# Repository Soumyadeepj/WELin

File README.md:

# WELin

WELin is a RFID based wireless inventory mangement system designed for , developed as a course project (EE344).<br>
It consists of 

> A light-weight wireless tag scanner with a custom PN532 reader module

> A userfriendly website and android application for tracking inventory

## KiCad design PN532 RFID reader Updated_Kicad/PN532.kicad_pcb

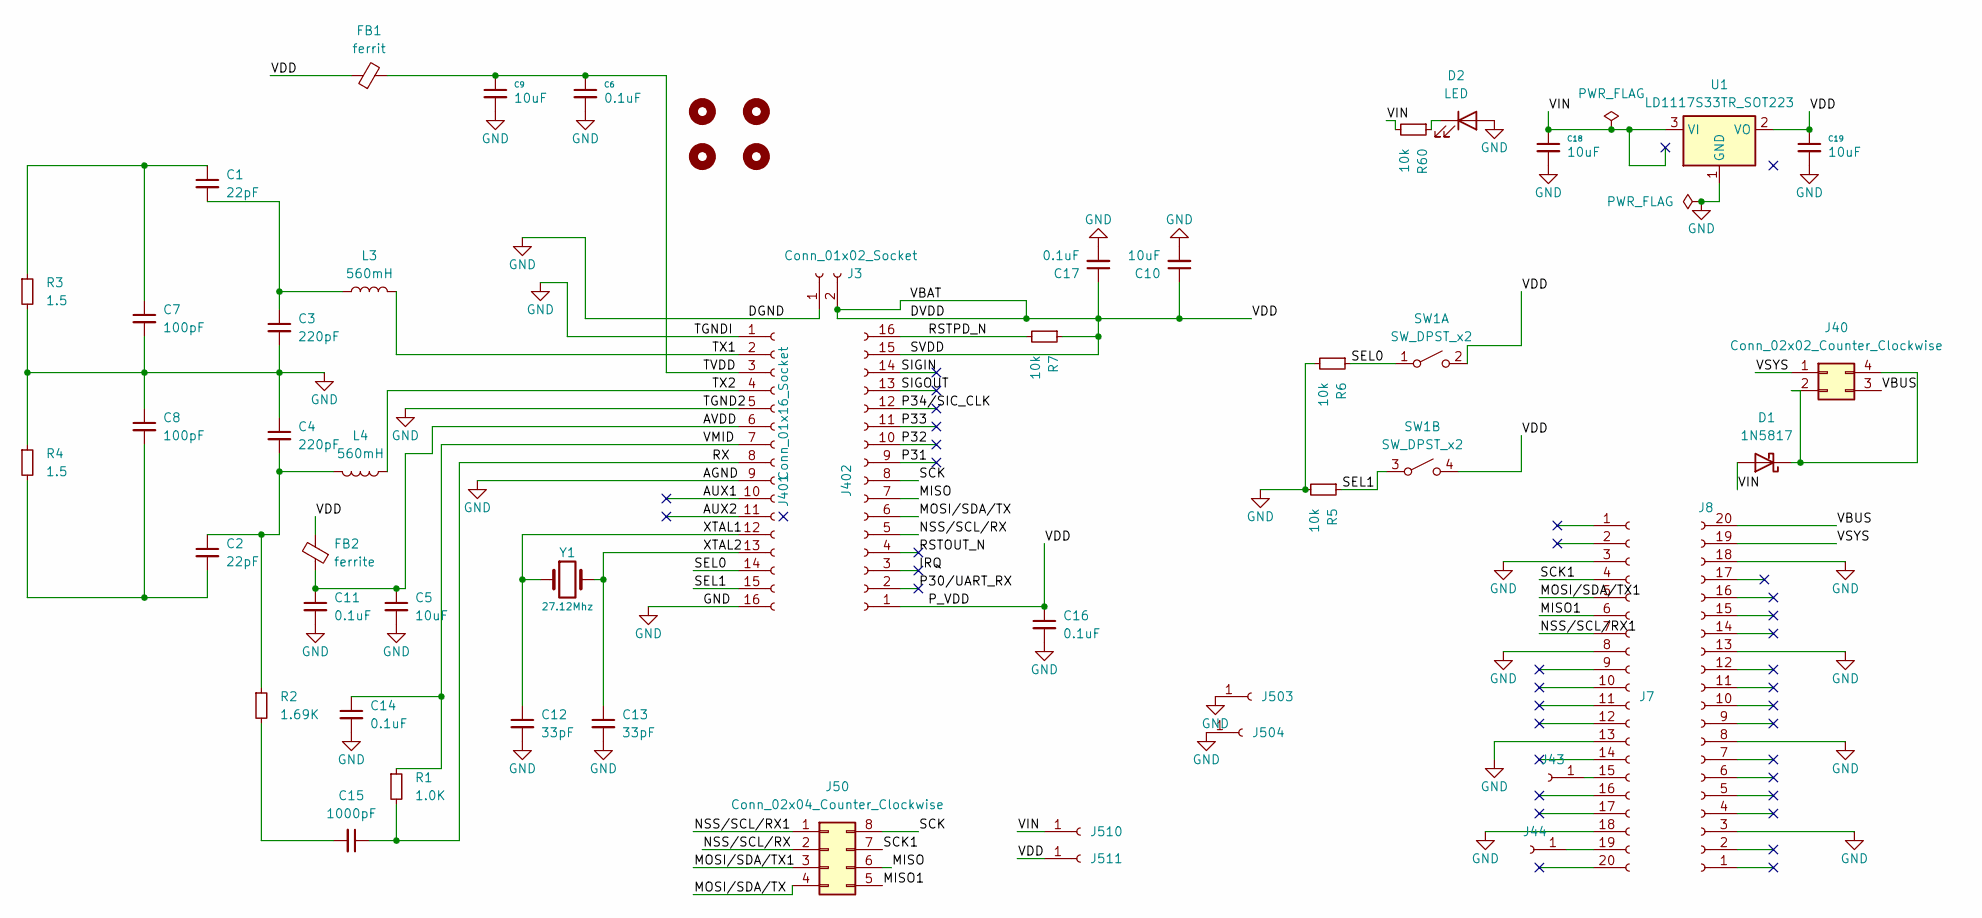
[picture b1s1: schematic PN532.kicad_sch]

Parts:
C1, C2: 22pF; C_1206_3216Metric_Pad1.33x1.80mm_HandSolder
C3, C4: 220pF; C_1206_3216Metric_Pad1.33x1.80mm_HandSolder
C5, C9, C10, C18, C19: 10uF; C_1206_3216Metric_Pad1.33x1.80mm_HandSolder
C6, C11, C14, C16, C17: 0.1uF; C_1206_3216Metric_Pad1.33x1.80mm_HandSolder
C7, C8: 100pF; C_1206_3216Metric_Pad1.33x1.80mm_HandSolder
C12, C13: 33pF; C_1206_3216Metric_Pad1.33x1.80mm_HandSolder
C15: 1000pF; C_1206_3216Metric_Pad1.33x1.80mm_HandSolder
D1: 1N5817; D_DO-41_SOD81_P10.16mm_Horizontal
D2: LED; C_0805_2012Metric_Pad1.18x1.45mm_HandSolder
FB1: ferrit; L_0805_2012Metric_Pad1.05x1.20mm_HandSolder
FB2: ferrite; L_0805_2012Metric_Pad1.05x1.20mm_HandSolder
H1, H2, H3, H4: MountingHole; MountingHole_2.5mm
J3: Conn_01x02_Socket; PinSocket_1x02_P2.54mm_Vertical
J7, J8: Conn_01x20_Socket; PinSocket_1x20_P2.54mm_Vertical
J40: Conn_02x02_Counter_Clockwise; PinSocket_2x02_P2.54mm_Vertical
J43, J44, J503, J504, J510, J511: Conn_01x01_Socket; PinSocket_1x01_P2.54mm_Vertical
J50: Conn_02x04_Counter_Clockwise; PinHeader_2x04_P2.54mm_Vertical
J401, J402: Conn_01x16_Socket; PinSocket_1x16_P2.54mm_Vertical
L3, L4: 560mH; L_0603_1608Metric_Pad1.05x0.95mm_HandSolder
R1: 1.0K; R_1206_3216Metric_Pad1.30x1.75mm_HandSolder
R2: 1.69K; R_1206_3216Metric_Pad1.30x1.75mm_HandSolder
R3, R4: 1.5; R_1206_3216Metric_Pad1.30x1.75mm_HandSolder
R5, R6, R7, R60: 10k; R_0805_2012Metric_Pad1.20x1.40mm_HandSolder
SW1: SW_DPST_x2; SW_DIP_SPSTx02_Slide_6.7x6.64mm_W7.62mm_P2.54mm_LowProfile
U1: LD1117S33TR_SOT223; SOT-223-3_TabPin2
Y1: 27.12Mhz; Crystal_HC49-U_Vertical

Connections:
/AUX1: J401.10
/AUX2: J401.11
/AVDD: C5.1, C11.1, FB2.1, J401.6
/DVDD: C10.1, C16.1, C17.1, C19.1, FB1.1, FB2.2, J3.2, J402.1, J402.15, J511.1, R7.1, SW1.2 (B), SW1.4 (B), U1.2 (VO)
/IRQ: J402.3
/MISO: J50.6, J402.7
/MISO1: J7.6, J50.5
/MOSI/SDA/TX: J50.4, J402.6
/MOSI/SDA/TX1: J7.5, J50.3
/NSS/SCL/RX: J50.2, J402.5
/NSS/SCL/RX1: J7.7, J50.1
/P30/UART_RX: J402.2
/P31: J402.9
/P32: J402.10
/P33: J402.11
/P34/SIC_CLK: J402.12
/RSTOUT_N: J402.4
/RSTPD_N: J402.16, R7.2
/RX: C15.1, J401.8, R1.2
/SCK: J50.8, J402.8
/SCK1: J7.4, J50.7
/SEL0: J401.14, R6.1, SW1.1 (A)
/SEL1: J401.15, R5.1, SW1.3 (A)
/SIGIN: J402.14
/SIGOUT: J402.13
/TVDD: C6.1, C9.1, FB1.2, J401.3
/TX1: J401.2, L3.2
/TX2: J401.4, L4.1
/VBUS: J8.20, J40.3
/VIN: C18.1, D1.2 (A), J510.1, R60.2, U1.3 (VI)
/VMID: C14.1, J401.7, R1.1
/VSYS: J8.19, J40.1
/XTAL1: C12.1, J401.12, Y1.1
/XTAL2: C13.1, J401.13, Y1.2
GND: C3.2, C4.1, C5.2, C6.2, C7.2, C8.1, C9.2, C10.2, C11.2, C12.2, C13.2, C14.2, C16.2, C17.2, C18.2, C19.2, D2.2 (A), J3.1, J7.3, J7.8, J7.13, J7.18, J8.3, J8.8, J8.13, J8.18, J401.1, J401.5, J401.9, J401.16, J503.1, J504.1, R3.2, R4.1, R5.2, R6.2, U1.1 (GND); also elsewhere on the board
unnamed: C1.1, C7.1, R3.1
unnamed: C1.2, C3.1, L3.1
unnamed: C2.1, C4.2, L4.2, R2.1
unnamed: C2.2, C8.2, R4.2
unnamed: C15.2, R2.2
unnamed: D1.1 (K), J40.2, J40.4
unnamed 41: D2.1 (K), R60.1; also elsewhere on the board
unnamed: J7.15, J43.1
unnamed: J7.19, J44.1

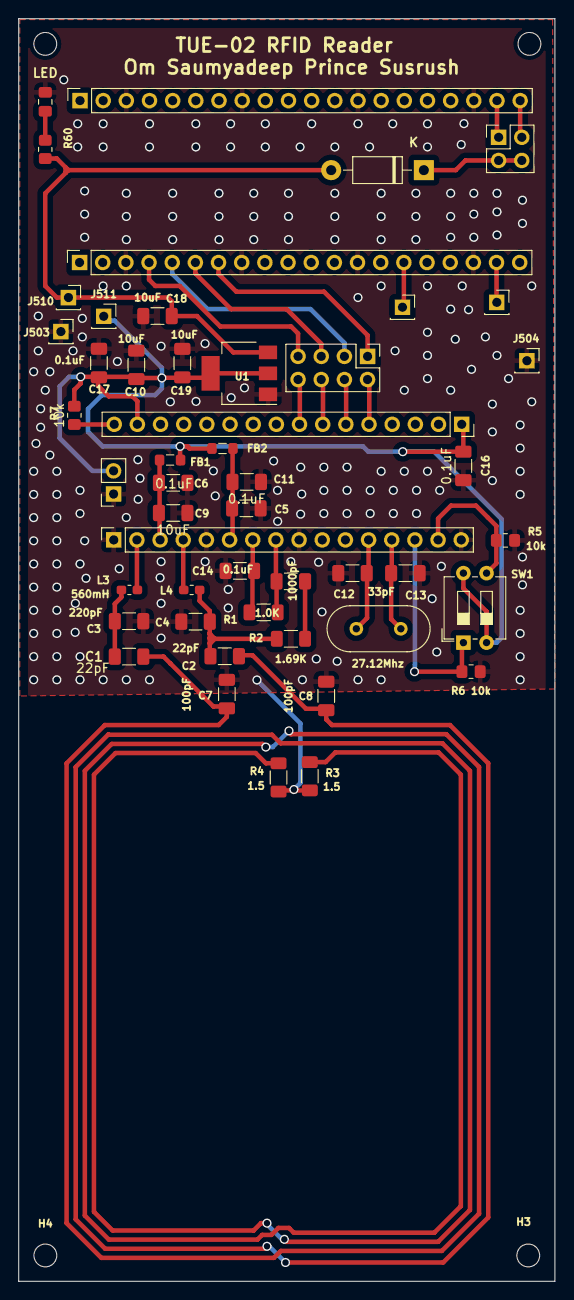
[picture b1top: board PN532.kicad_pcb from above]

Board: 2 copper layers, 58.8 x 138.4 mm, 53 parts (0 on the bottom side), 33 nets.

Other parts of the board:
LED: LED; C_0805_2012Metric_Pad1.18x1.45mm_HandSolder

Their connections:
GND: LED.2 (A); also elsewhere on the board
unnamed 41: LED.1 (K); also elsewhere on the board

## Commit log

2024-04-19 Completed
2024-04-19 Upadated manual
